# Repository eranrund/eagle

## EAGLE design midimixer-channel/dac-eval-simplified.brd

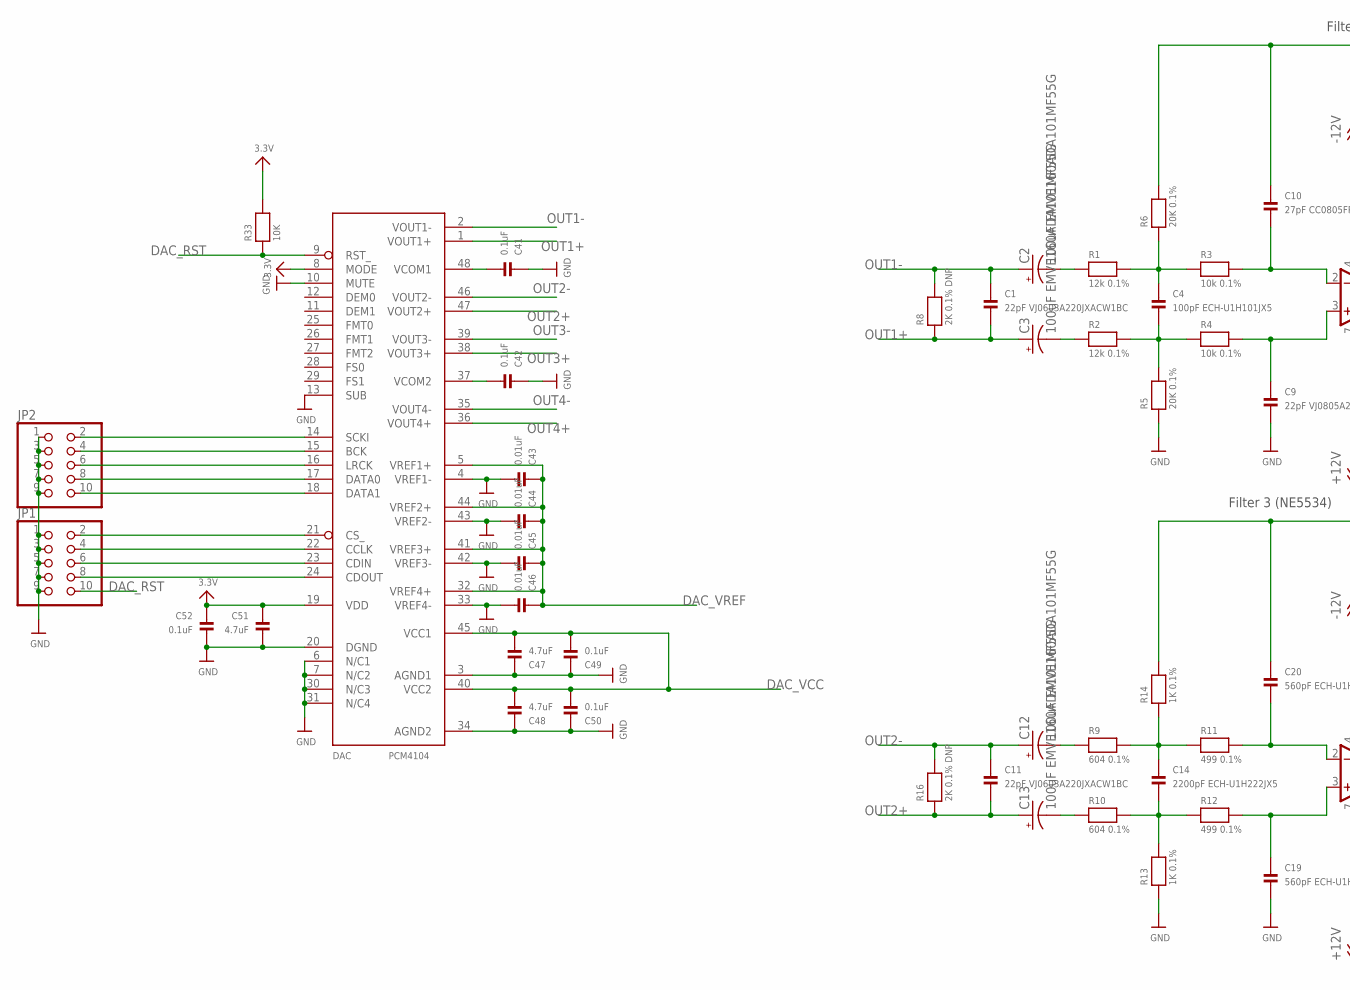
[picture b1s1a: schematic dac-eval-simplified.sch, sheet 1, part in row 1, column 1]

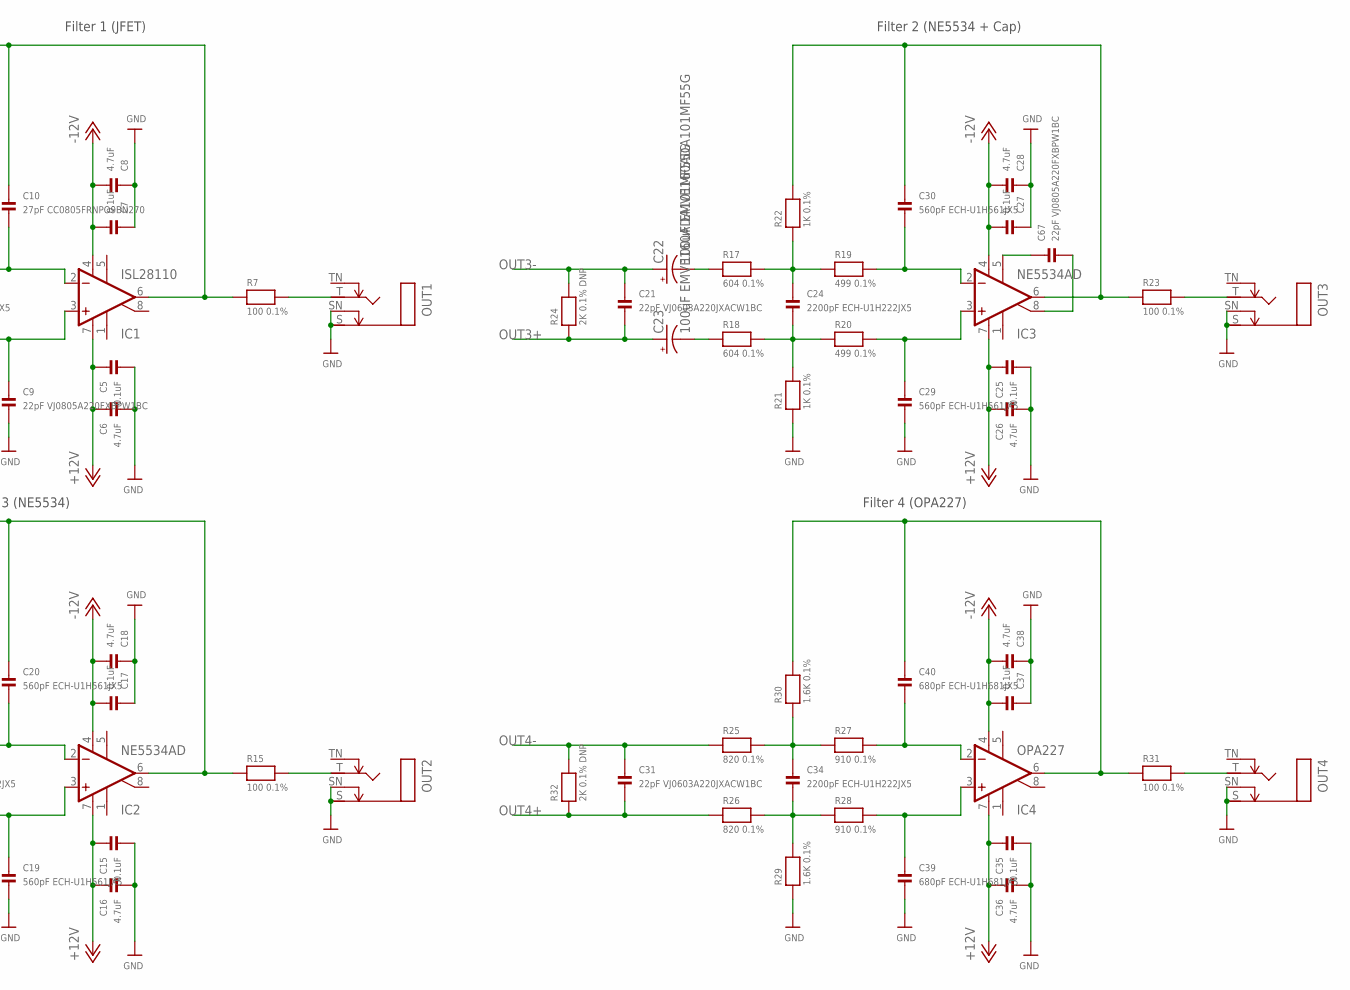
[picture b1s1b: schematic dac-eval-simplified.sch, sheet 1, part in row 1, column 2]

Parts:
C1, C11, C21, C31: 22pF VJ0603A220JXACW1BC; 0603
C2, C3, C12, C13, C22, C23: 100uF EMVE160ADA101MF55G; PANASONIC_D
C4: 100pF ECH-U1H101JX5; 0805
C5, C7, C15, C17, C25, C27, C35, C37, C41, C42, C49, C50, C52: 0.1uF; 0603
C6, C8, C16, C18, C26, C28, C36, C38, C47, C48, C51: 4.7uF; 0603
C9, C67: 22pF VJ0805A220FXBPW1BC; 0805
C10: 27pF CC0805FRNPO9BN270; 0805
C14, C24, C34: 2200pF ECH-U1H222JX5; 0805
C19, C20, C29, C30: 560pF ECH-U1H561JX5; 0805
C39, C40: 680pF ECH-U1H681JX5; 0805
C43, C44, C45, C46: 0.01uF; 0603
DAC: PCM4104; SQFP-S-7X7-48
IC1: ISL28110; SO08
IC2, IC3: NE5534AD; SO08
IC4: OPA227; SO08
JP1, JP2: HEADER-2X5; 2X05
OUT1, OUT2, OUT3, OUT4: NMJ4HFD2; NMJ4HC-S
R1, R2: 12k 0.1%; 0603
R3, R4: 10k 0.1%; 0603
R5, R6: 20K 0.1%; 0603
R7, R15, R23, R31: 100 0.1%; 0603
R8, R16, R24, R32: 2K 0.1% DNP; 0603
R9, R10, R17, R18: 604 0.1%; 0603
R11, R12, R19, R20: 499 0.1%; 0603
R13, R14, R21, R22: 1K 0.1%; 0603
R25, R26: 820 0.1%; 0603
R27, R28: 910 0.1%; 0603
R29, R30: 1.6K 0.1%; 0603
R33: 10K; 0603

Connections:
3.3V: C51.1, C52.1, DAC.8 (MODE), DAC.19 (VDD), R33.2; also elsewhere on the board
+12V: C5.1, C6.1, C15.1, C16.1, C25.1, C26.1, C35.1, C36.1, IC1.7 (V+), IC2.7 (V+), IC3.7 (V+), IC4.7 (V+); also elsewhere on the board
-12V: C7.2, C8.2, C17.2, C18.2, C27.2, C28.2, C37.2, C38.2, IC1.4 (V-), IC2.4 (V-), IC3.4 (V-), IC4.4 (V-); also elsewhere on the board
DAC_BCK: DAC.15 (BCK), JP2.4
DAC_CLK: DAC.22 (CCLK), JP1.4
DAC_CS: DAC.21 (CS_), JP1.2
DAC_D0: DAC.17 (DATA0), JP2.8
DAC_D1: DAC.18 (DATA1), JP2.10
DAC_LRCK: DAC.16 (LRCK), JP2.6
DAC_MISO: DAC.24 (CDOUT), JP1.8
DAC_MOSI: DAC.23 (CDIN), JP1.6
DAC_RST: DAC.9 (RST_), JP1.10, R33.1
DAC_SCK: DAC.14 (SCKI), JP2.2
DAC_VCC: C47.2, C48.2, C49.2, C50.2, DAC.40 (VCC2), DAC.45 (VCC1); also elsewhere on the board
DAC_VREF: C43.1, C44.1, C45.1, C46.1, DAC.5 (VREF1+), DAC.32 (VREF4+), DAC.41 (VREF3+), DAC.44 (VREF2+); also elsewhere on the board
GND: C5.2, C6.2, C7.1, C8.1, C9.2, C15.2, C16.2, C17.1, C18.1, C19.2, C25.2, C26.2, C27.1, C28.1, C29.2, C35.2, C36.2, C37.1, C38.1, C39.2, C41.1, C42.1, C43.2, C44.2, C45.2, C46.2, C47.1, C48.1, C49.1, C50.1, C51.2, C52.2, DAC.3 (AGND1), DAC.4 (VREF1-), DAC.6 (N/C1), DAC.7 (N/C2), DAC.10 (MUTE), DAC.13 (SUB), DAC.20 (DGND), DAC.30 (N/C3), DAC.31 (N/C4), DAC.33 (VREF4-), DAC.34 (AGND2), DAC.42 (VREF3-), DAC.43 (VREF2-), JP1.1, JP1.3, JP1.5, JP1.7, JP1.9, JP2.1, JP2.3, JP2.5, JP2.7, JP2.9, OUT1.S, OUT1.SN, OUT2.S, OUT2.SN, OUT3.S, OUT3.SN, OUT4.S, OUT4.SN, R5.1, R13.1, R21.1, R29.1; also elsewhere on the board
unnamed: C12.-, R9.1
unnamed: C13.-, R10.1
unnamed: C2.-, R1.1
unnamed: C3.-, R2.1
unnamed: C4.2, R2.2, R4.1, R5.2
unnamed: C4.1, R1.2, R3.1, R6.1
unnamed: C14.2, R10.2, R12.1, R13.2
unnamed: C9.1, IC1.3 (+IN), R4.2
unnamed: C10.2, IC1.2 (-IN), R3.2
unnamed: C10.1, IC1.6 (OUT), R6.2, R7.1
unnamed: C14.1, R9.2, R11.1, R14.1
unnamed: OUT1.T, R7.2
unnamed: C19.1, IC2.3 (+IN), R12.2
unnamed: C20.2, IC2.2 (-IN), R11.2
unnamed: C20.1, IC2.6 (OUT), R14.2, R15.1
unnamed: OUT2.T, R15.2
unnamed: C22.-, R17.1
unnamed: C23.-, R18.1
unnamed: C24.2, R18.2, R20.1, R21.2
unnamed: C24.1, R17.2, R19.1, R22.1
unnamed: C29.1, IC3.3 (+IN), R20.2
unnamed: C30.2, IC3.2 (-IN), R19.2
unnamed: C30.1, IC3.6 (OUT), R22.2, R23.1
unnamed: OUT3.T, R23.2
unnamed: C34.2, R26.2, R28.1, R29.2
unnamed: C34.1, R25.2, R27.1, R30.1
unnamed: C39.1, IC4.3 (+IN), R28.2
unnamed: C40.2, IC4.2 (-IN), R27.2
unnamed: C40.1, IC4.6 (OUT), R30.2, R31.1
unnamed: OUT4.T, R31.2
unnamed: C41.2, DAC.48 (VCOM1)
unnamed: C42.2, DAC.37 (VCOM2)
unnamed: C67.1, IC3.5 (CMP)
unnamed: C67.2, IC3.8 (ON/CMP)
OUT1+: C1.2, C3.+, DAC.1 (VOUT1+), R8.1
OUT1-: C1.1, C2.+, DAC.2 (VOUT1-), R8.2
OUT2+: C11.2, C13.+, DAC.47 (VOUT2+), R16.1
OUT2-: C11.1, C12.+, DAC.46 (VOUT2-), R16.2
OUT3+: C21.2, C23.+, DAC.38 (VOUT3+), R24.1
OUT3-: C21.1, C22.+, DAC.39 (VOUT3-), R24.2
OUT4+: C31.2, DAC.36 (VOUT4+), R26.1, R32.1
OUT4-: C31.1, DAC.35 (VOUT4-), R25.1, R32.2

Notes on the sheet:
Filter 1 (JFET)
Filter 2 (NE5534 + Cap)
Filter 3 (NE5534)
Filter 4 (OPA227)

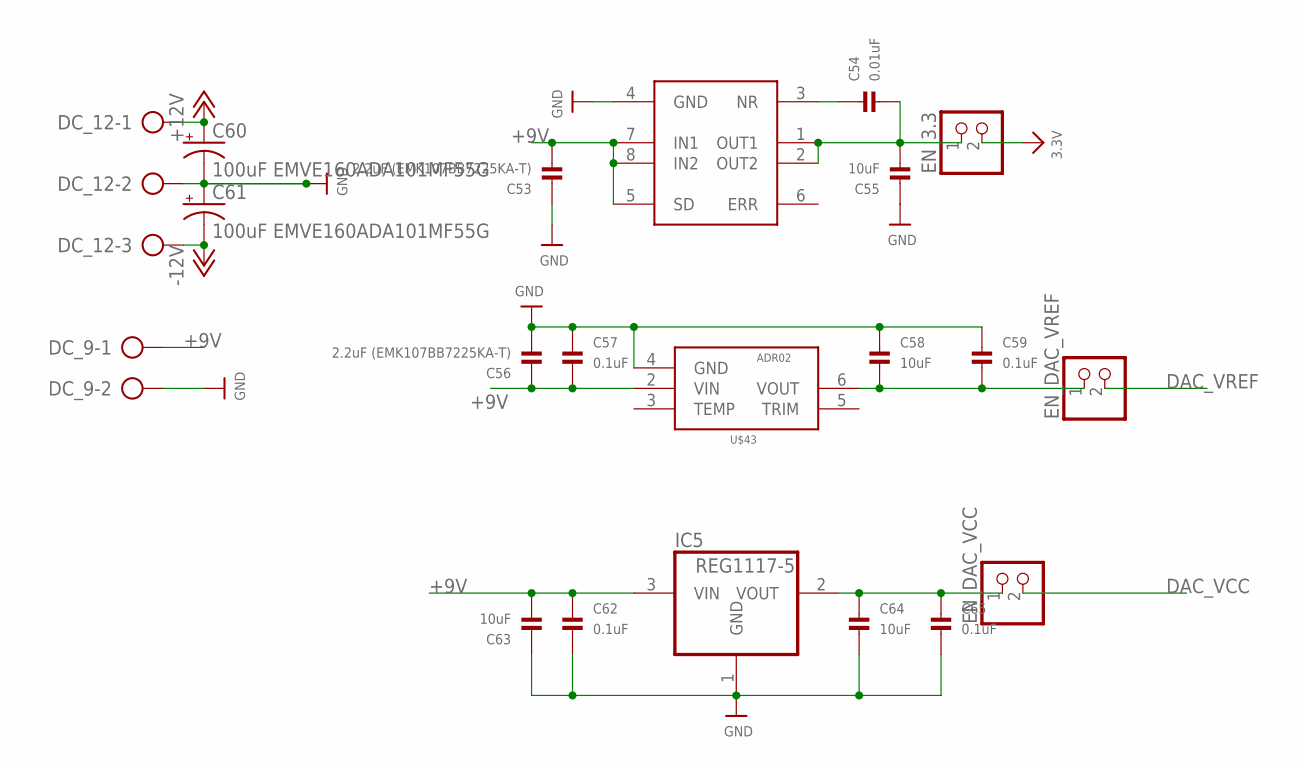
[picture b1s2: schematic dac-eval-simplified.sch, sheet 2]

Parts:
C53, C56: 2.2uF (EMK107BB7225KA-T); 0603
C54: 0.01uF; 0603
C55, C58, C63, C64: 10uF; 0603
C57, C59, C62, C65: 0.1uF; 0603
C60, C61: 100uF EMVE160ADA101MF55G; PANASONIC_D
DC_9: AK500/2
DC_12: AK500/3
EN_3.3: HEADER-1X2; 1X02_OVAL
EN_DAC_VCC: HEADER-1X2; 1X02_OVAL
EN_DAC_VREF: HEADER-1X2; 1X02_OVAL
IC5: REG1117-5; SOT223
U$30: ADP3301ARZ-3.3; SO08
U$43: ADR02; SOIC8

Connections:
3.3V: EN_3.3.2; also elsewhere on the board
+9V: C53.2, C56.1, C57.2, C62.1, C63.2, DC_9.1, IC5.3 (VIN), U$30.5 (SD), U$30.7 (IN1), U$30.8 (IN2), U$43.2 (VIN)
+12V: C60.+, DC_12.1; also elsewhere on the board
-12V: C61.-, DC_12.3; also elsewhere on the board
DAC_VCC: EN_DAC_VCC.2; also elsewhere on the board
DAC_VREF: EN_DAC_VREF.2; also elsewhere on the board
GND: C53.1, C55.1, C56.2, C57.1, C58.1, C59.1, C60.-, C61.+, C62.2, C63.1, C64.2, C65.2, DC_9.2, DC_12.2, IC5.1 (GND), U$30.4 (GND), U$43.4 (GND); also elsewhere on the board
unnamed: C54.2, C55.2, EN_3.3.1, U$30.1 (OUT1), U$30.2 (OUT2)
unnamed: C54.1, U$30.3 (NR)
unnamed: C58.2, C59.2, EN_DAC_VREF.1, U$43.6 (VOUT)
unnamed: C64.1, C65.1, EN_DAC_VCC.1, IC5.2 (VOUT)

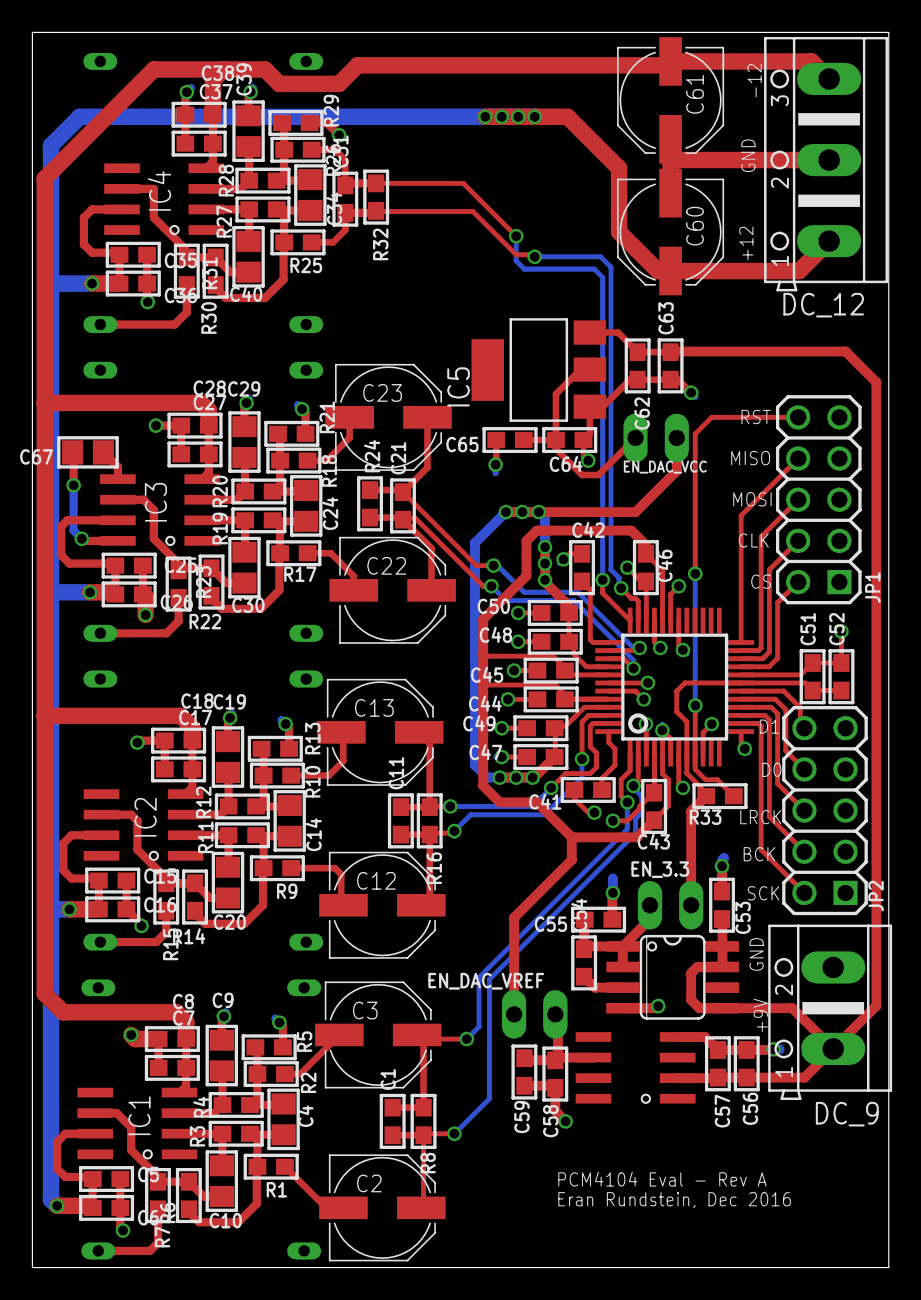
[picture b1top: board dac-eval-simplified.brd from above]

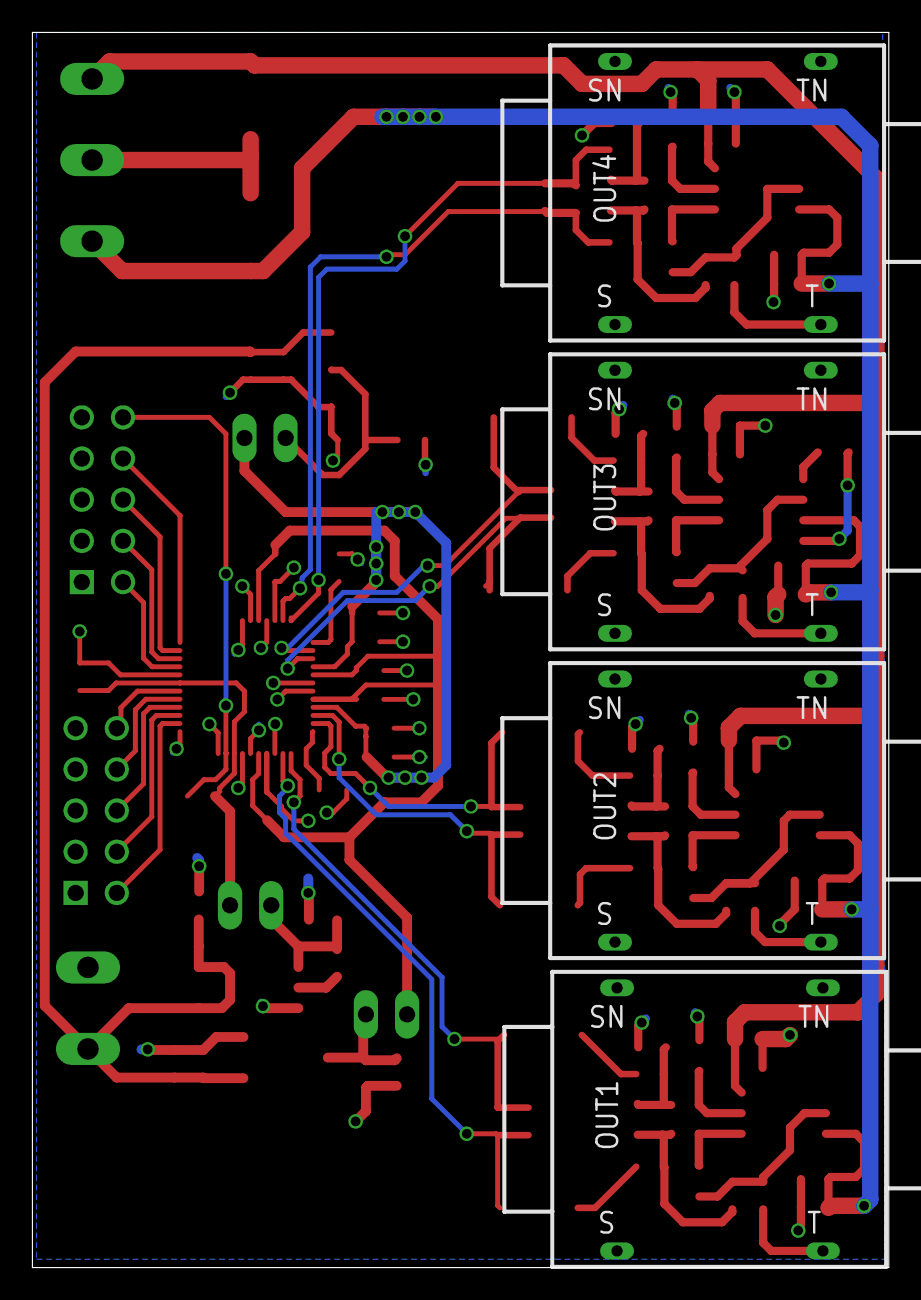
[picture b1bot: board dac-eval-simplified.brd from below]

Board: 2 copper layers, 52.8 x 76.2 mm, 116 parts (4 on the bottom side), 63 nets.

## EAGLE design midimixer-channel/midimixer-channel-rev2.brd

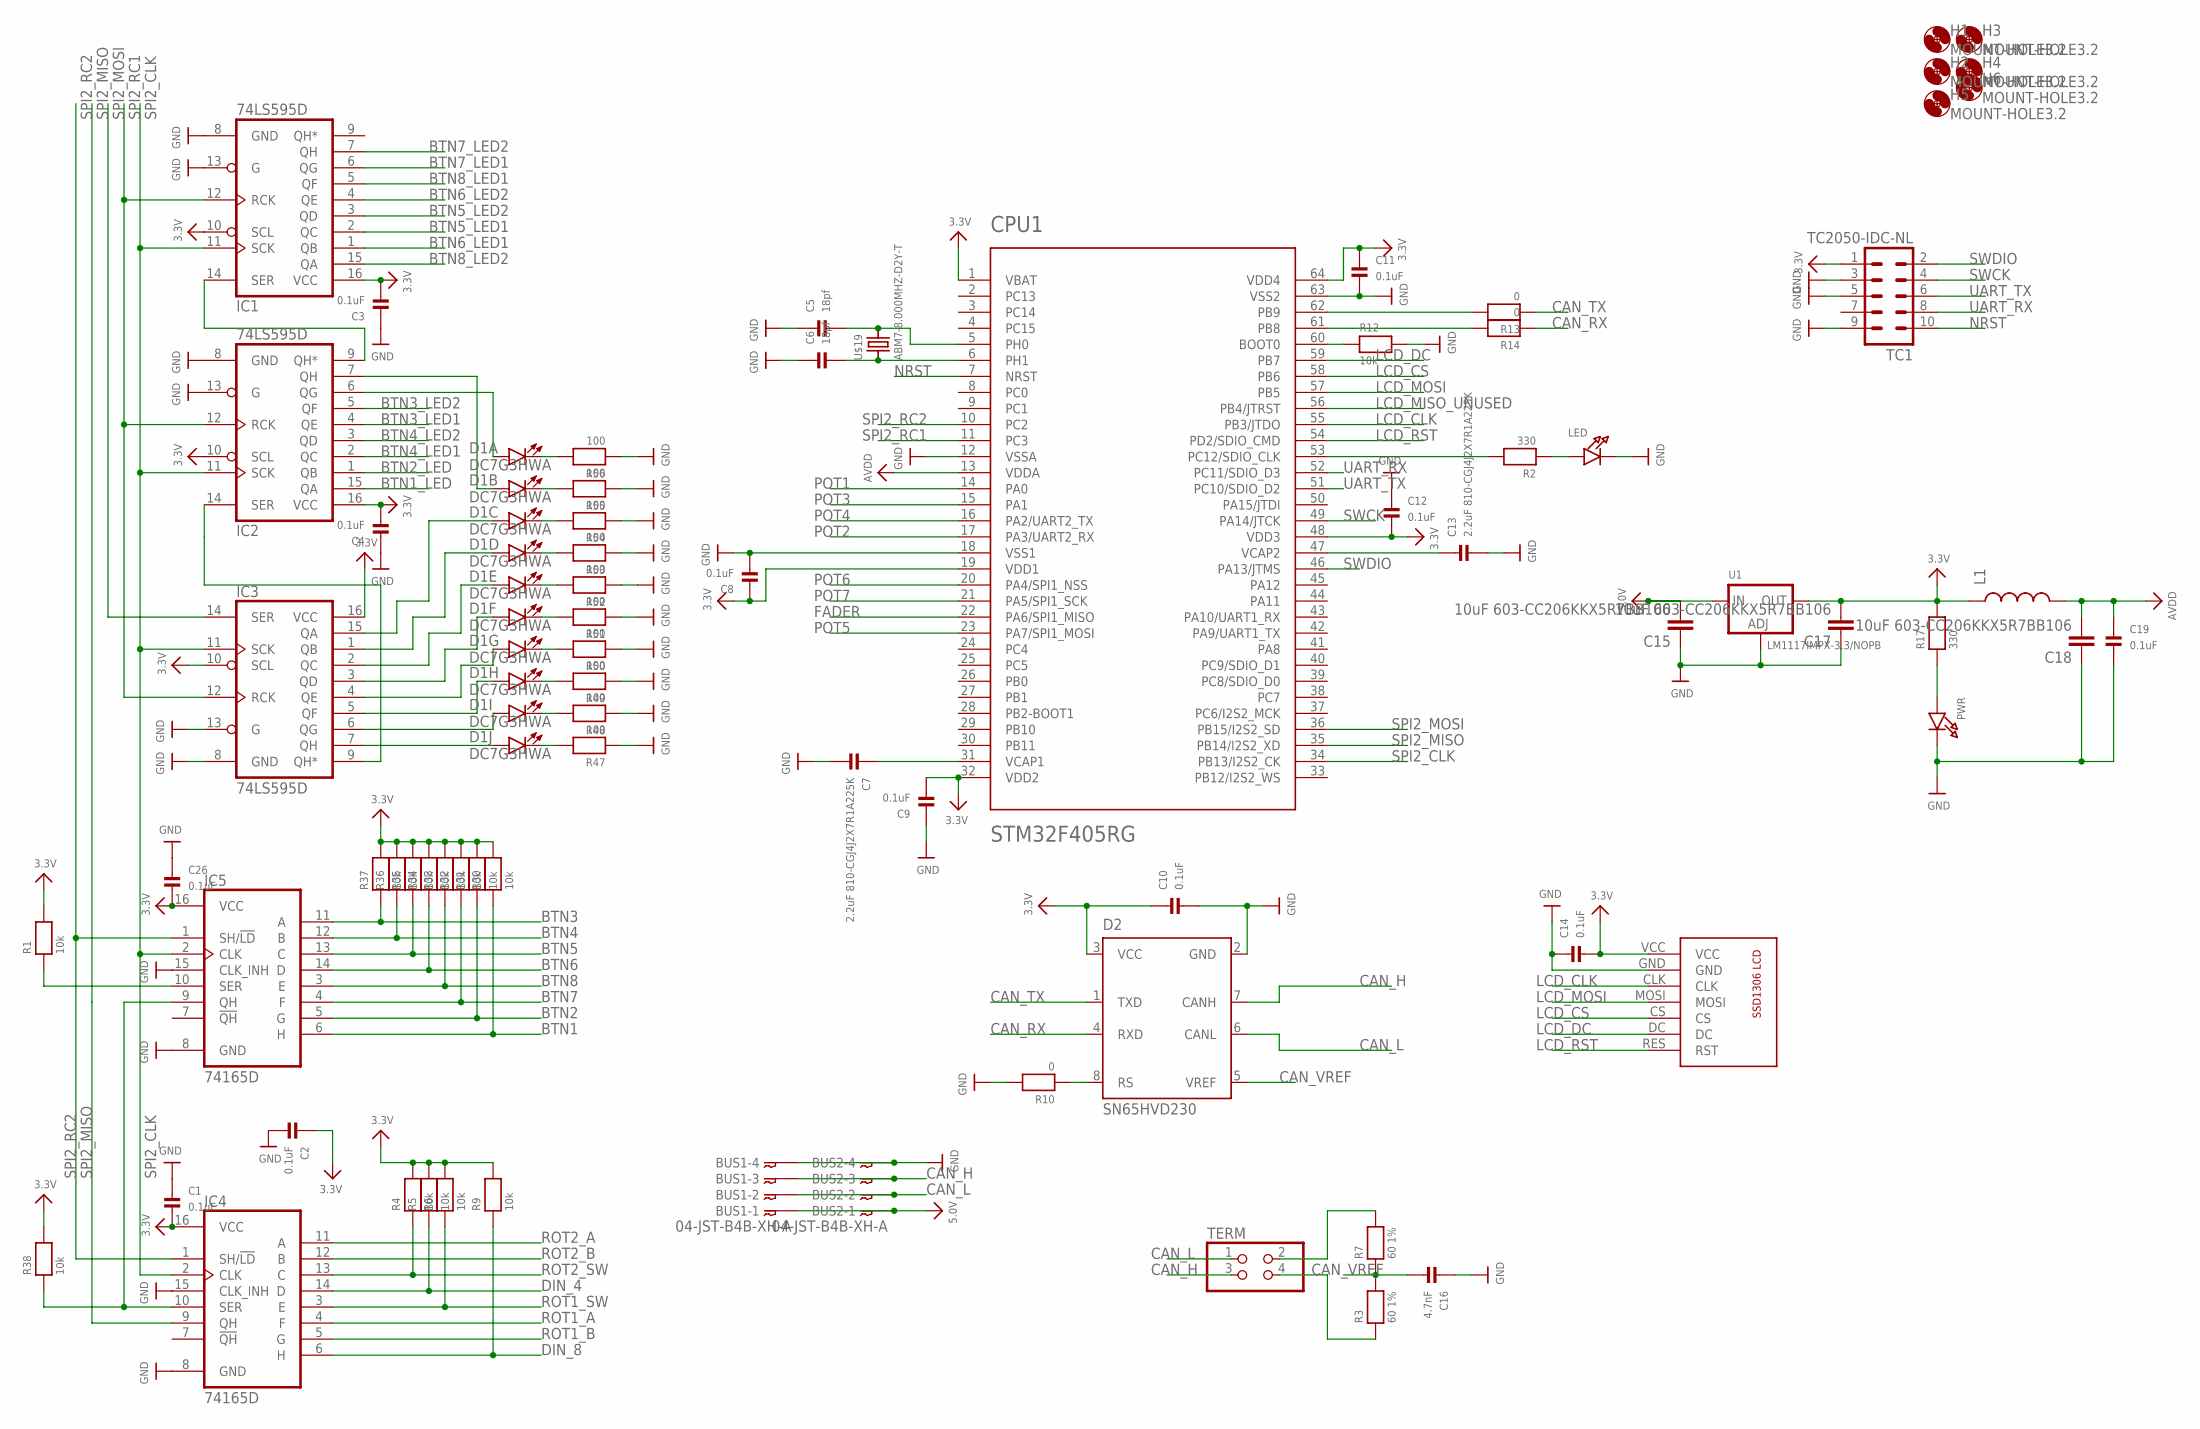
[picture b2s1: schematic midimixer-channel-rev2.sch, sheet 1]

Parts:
BUS1, BUS2: 04-JST-B4B-XH-A; B4B-XH
C1, C2, C3, C4, C8, C9, C10, C11, C12, C14, C19, C26: 0.1uF; 0603
C5, C6: 18pf; 0603
C7, C13: 2.2uF 810-CGJ4J2X7R1A225K; 0805; MPN CGJ4J2X7R1A225K125AA
C15, C17, C18: 10uF 603-CC206KKX5R7BB106; 1206; MPN CC1206KKX5R7BB106
C16: 4.7nF; 0603
CPU1: STM32F405RG; TQFP64; MPN STM32F405RGT6
D1: DC7G3HWA; LED_BARGAPH_10
D2: SN65HVD230; SO8
H1, H2, H3, H4, H5, H6: MOUNT-HOLE3.2; 3,2
IC1, IC2, IC3: 74LS595D; SO16
IC4, IC5: 74165D; SO16
L1: INDUCTOR0805; 0805; MPN 2508056017Y2
LCD: SSD1306-7PINWITHOUT-HOLES; SSD1306-7PIN-NO-HOLES
LED: LED0603; CHIPLED_0603
PWR: LED0603; CHIPLED_0603
R1, R4, R5, R6, R9, R12, R30, R31, R32, R33, R34, R35, R36, R37, R38: 10k; _0603
R2, R17: 330; 0603
R3, R7: 60 1%; 0603; MPN MF-RES-0603-60.4
R10, R13, R14: 0; _0603
R47, R48, R49, R50, R51, R52, R53, R54, R55, R56: 100; _0603
TC1: TC2050-IDC-NL
TERM: PINHD-2X2; 2X02
U1: LM1117IMPX-3.3/NOPB; SOT223-R
U$19: ABM7-8.000MHZ-D2Y-T

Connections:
3.3V: C1.2, C2.1, C3.2, C4.2, C8.1, C9.2, C10.1, C11.1, C12.2, C14.2, C17.2, C26.2, CPU1.1 (VBAT), CPU1.19 (VDD1), CPU1.32 (VDD2), CPU1.48 (VDD3), CPU1.64 (VDD4), D2.3 (VCC), IC1.10 (SCL), IC1.16 (VCC), IC2.10 (SCL), IC2.16 (VCC), IC3.10 (SCL), IC3.16 (VCC), IC4.16 (VCC), IC5.16 (VCC), L1.1, LCD.VCC, R1.2, R4.2, R5.2, R6.2, R9.2, R17.2, R30.2, R31.2, R32.2, R33.2, R34.2, R35.2, R36.2, R37.2, R38.2, TC1.1, U1.2 (OUT); also elsewhere on the board
5.0V: BUS1.P$1, BUS2.P$1, C15.2, U1.3 (IN); also elsewhere on the board
AVDD: C18.2, C19.1, CPU1.13 (VDDA), L1.2
BTN1: IC5.6 (H), R30.1; also elsewhere on the board
BTN1_LED: IC2.15 (QA); also elsewhere on the board
BTN2: IC5.5 (G), R31.1; also elsewhere on the board
BTN2_LED: IC2.1 (QB); also elsewhere on the board
BTN3: IC5.11 (A), R37.1; also elsewhere on the board
BTN3_LED1: IC2.4 (QE); also elsewhere on the board
BTN3_LED2: IC2.5 (QF); also elsewhere on the board
BTN4: IC5.12 (B), R36.1; also elsewhere on the board
BTN4_LED1: IC2.2 (QC); also elsewhere on the board
BTN4_LED2: IC2.3 (QD); also elsewhere on the board
BTN5: IC5.13 (C), R35.1; also elsewhere on the board
BTN5_LED1: IC1.2 (QC); also elsewhere on the board
BTN5_LED2: IC1.3 (QD); also elsewhere on the board
BTN6: IC5.14 (D), R34.1; also elsewhere on the board
BTN6_LED1: IC1.1 (QB); also elsewhere on the board
BTN6_LED2: IC1.4 (QE); also elsewhere on the board
BTN7: IC5.4 (F), R32.1; also elsewhere on the board
BTN7_LED1: IC1.6 (QG); also elsewhere on the board
BTN7_LED2: IC1.7 (QH); also elsewhere on the board
BTN8: IC5.3 (E), R33.1; also elsewhere on the board
BTN8_LED1: IC1.5 (QF); also elsewhere on the board
BTN8_LED2: IC1.15 (QA); also elsewhere on the board
CAN_H: BUS1.P$3, BUS2.P$3, D2.7 (CANH), TERM.3
CAN_L: BUS1.P$2, BUS2.P$2, D2.6 (CANL), TERM.1
CAN_RX: D2.4 (RXD), R14.1
CAN_TX: D2.1 (TXD), R13.1
CAN_VREF: C16.2, D2.5 (VREF), R3.2, R7.1
DIN_4: IC4.14 (D), R5.1
DIN_8: IC4.6 (H), R9.1
FADER: CPU1.22 (PA6/SPI1_MISO); also elsewhere on the board
GND: BUS1.P$4, BUS2.P$4, C1.1, C2.2, C3.1, C4.1, C5.1, C6.1, C7.2, C8.2, C9.1, C10.2, C11.2, C12.1, C13.2, C14.1, C15.1, C16.1, C17.1, C18.1, C19.2, C26.1, CPU1.12 (VSSA), CPU1.18 (VSS1), CPU1.63 (VSS2), D2.2 (GND), IC1.8 (GND), IC1.13 (G), IC2.8 (GND), IC2.13 (G), IC3.8 (GND), IC3.13 (G), IC4.8 (GND), IC4.15 (CLK_INH), IC5.8 (GND), IC5.15 (CLK_INH), LCD.GND, LED.C, PWR.C, R10.2, R12.2, R47.1, R48.1, R49.1, R50.1, R51.1, R52.1, R53.1, R54.1, R55.1, R56.1, TC1.3, TC1.5, TC1.9, U1.1 (ADJ); also elsewhere on the board
LCD_CLK: CPU1.55 (PB3/JTDO), LCD.CLK
LCD_CS: CPU1.58 (PB6), LCD.CS
LCD_DC: CPU1.59 (PB7), LCD.DC
LCD_MISO_UNUSED: CPU1.56 (PB4/JTRST)
LCD_MOSI: CPU1.57 (PB5), LCD.MOSI
LCD_RST: CPU1.54 (PD2/SDIO_CMD), LCD.RES (RST)
unnamed: C6.2, CPU1.6 (PH1), U$19.P$1 (1)
unnamed: C5.2, CPU1.5 (PH0), U$19.P$2 (2)
unnamed: C13.1, CPU1.47 (VCAP2)
unnamed: C7.1, CPU1.31 (VCAP1)
unnamed: PWR.A, R17.1
unnamed: CPU1.60 (BOOT0), R12.1
unnamed: D1.5 (A), IC3.2 (QC)
unnamed: D1.2 (A), IC2.7 (QH)
unnamed: D1.1 (A), IC2.6 (QG)
unnamed: IC1.14 (SER), IC2.9 (QH*)
unnamed: CPU1.62 (PB9), R13.2
unnamed: D1.11 (C), R47.2
unnamed: D1.12 (C), R48.2
unnamed: D1.13 (C), R49.2
unnamed: D1.14 (C), R50.2
unnamed: D1.15 (C), R51.2
unnamed: D1.16 (C), R52.2
unnamed: D1.17 (C), R53.2
unnamed: D1.18 (C), R54.2
unnamed: D1.19 (C), R55.2
unnamed: D1.20 (C), R56.2
unnamed: IC4.10 (SER), IC5.9 (QH), R38.1
unnamed: CPU1.61 (PB8), R14.2
unnamed: IC5.10 (SER), R1.1
unnamed: LED.A, R2.1
unnamed: D1.10 (A), IC3.7 (QH)
unnamed: D1.9 (A), IC3.6 (QG)
unnamed: D1.8 (A), IC3.5 (QF)
unnamed: CPU1.53 (PC12/SDIO_CLK), R2.2
unnamed: R7.2, TERM.2
unnamed: R3.1, TERM.4
unnamed: D1.7 (A), IC3.4 (QE)
unnamed: D1.6 (A), IC3.3 (QD)
unnamed: D1.4 (A), IC3.1 (QB)
unnamed: D1.3 (A), IC3.15 (QA)
unnamed: IC2.14 (SER), IC3.9 (QH*)
unnamed: D2.8 (RS), R10.1
NRST: CPU1.7 (NRST), TC1.10
POT1: CPU1.14 (PA0); also elsewhere on the board
POT2: CPU1.17 (PA3/UART2_RX); also elsewhere on the board
POT3: CPU1.15 (PA1); also elsewhere on the board
POT4: CPU1.16 (PA2/UART2_TX); also elsewhere on the board
POT5: CPU1.23 (PA7/SPI1_MOSI); also elsewhere on the board
POT6: CPU1.20 (PA4/SPI1_NSS); also elsewhere on the board
POT7: CPU1.21 (PA5/SPI1_SCK); also elsewhere on the board
ROT1_A: IC4.4 (F); also elsewhere on the board
ROT1_B: IC4.5 (G); also elsewhere on the board
ROT1_SW: IC4.3 (E), R6.1; also elsewhere on the board
ROT2_A: IC4.11 (A); also elsewhere on the board
ROT2_B: IC4.12 (B); also elsewhere on the board
ROT2_SW: IC4.13 (C), R4.1; also elsewhere on the board
SPI2_CLK: CPU1.34 (PB13/I2S2_CK), IC1.11 (SCK), IC2.11 (SCK), IC3.11 (SCK), IC4.2 (CLK), IC5.2 (CLK)
SPI2_MISO: CPU1.35 (PB14/I2S2_XD), IC4.9 (QH)
SPI2_MOSI: CPU1.36 (PB15/I2S2_SD), IC3.14 (SER)
SPI2_RC1: CPU1.11 (PC3), IC1.12 (RCK), IC2.12 (RCK), IC3.12 (RCK)
SPI2_RC2: CPU1.10 (PC2), IC4.1 (SH/!LD), IC5.1 (SH/!LD)
SWCK: CPU1.49 (PA14/JTCK), TC1.4
SWDIO: CPU1.46 (PA13/JTMS), TC1.2
UART_RX: CPU1.52 (PC11/SDIO_D3), TC1.8
UART_TX: CPU1.51 (PC10/SDIO_D2), TC1.6

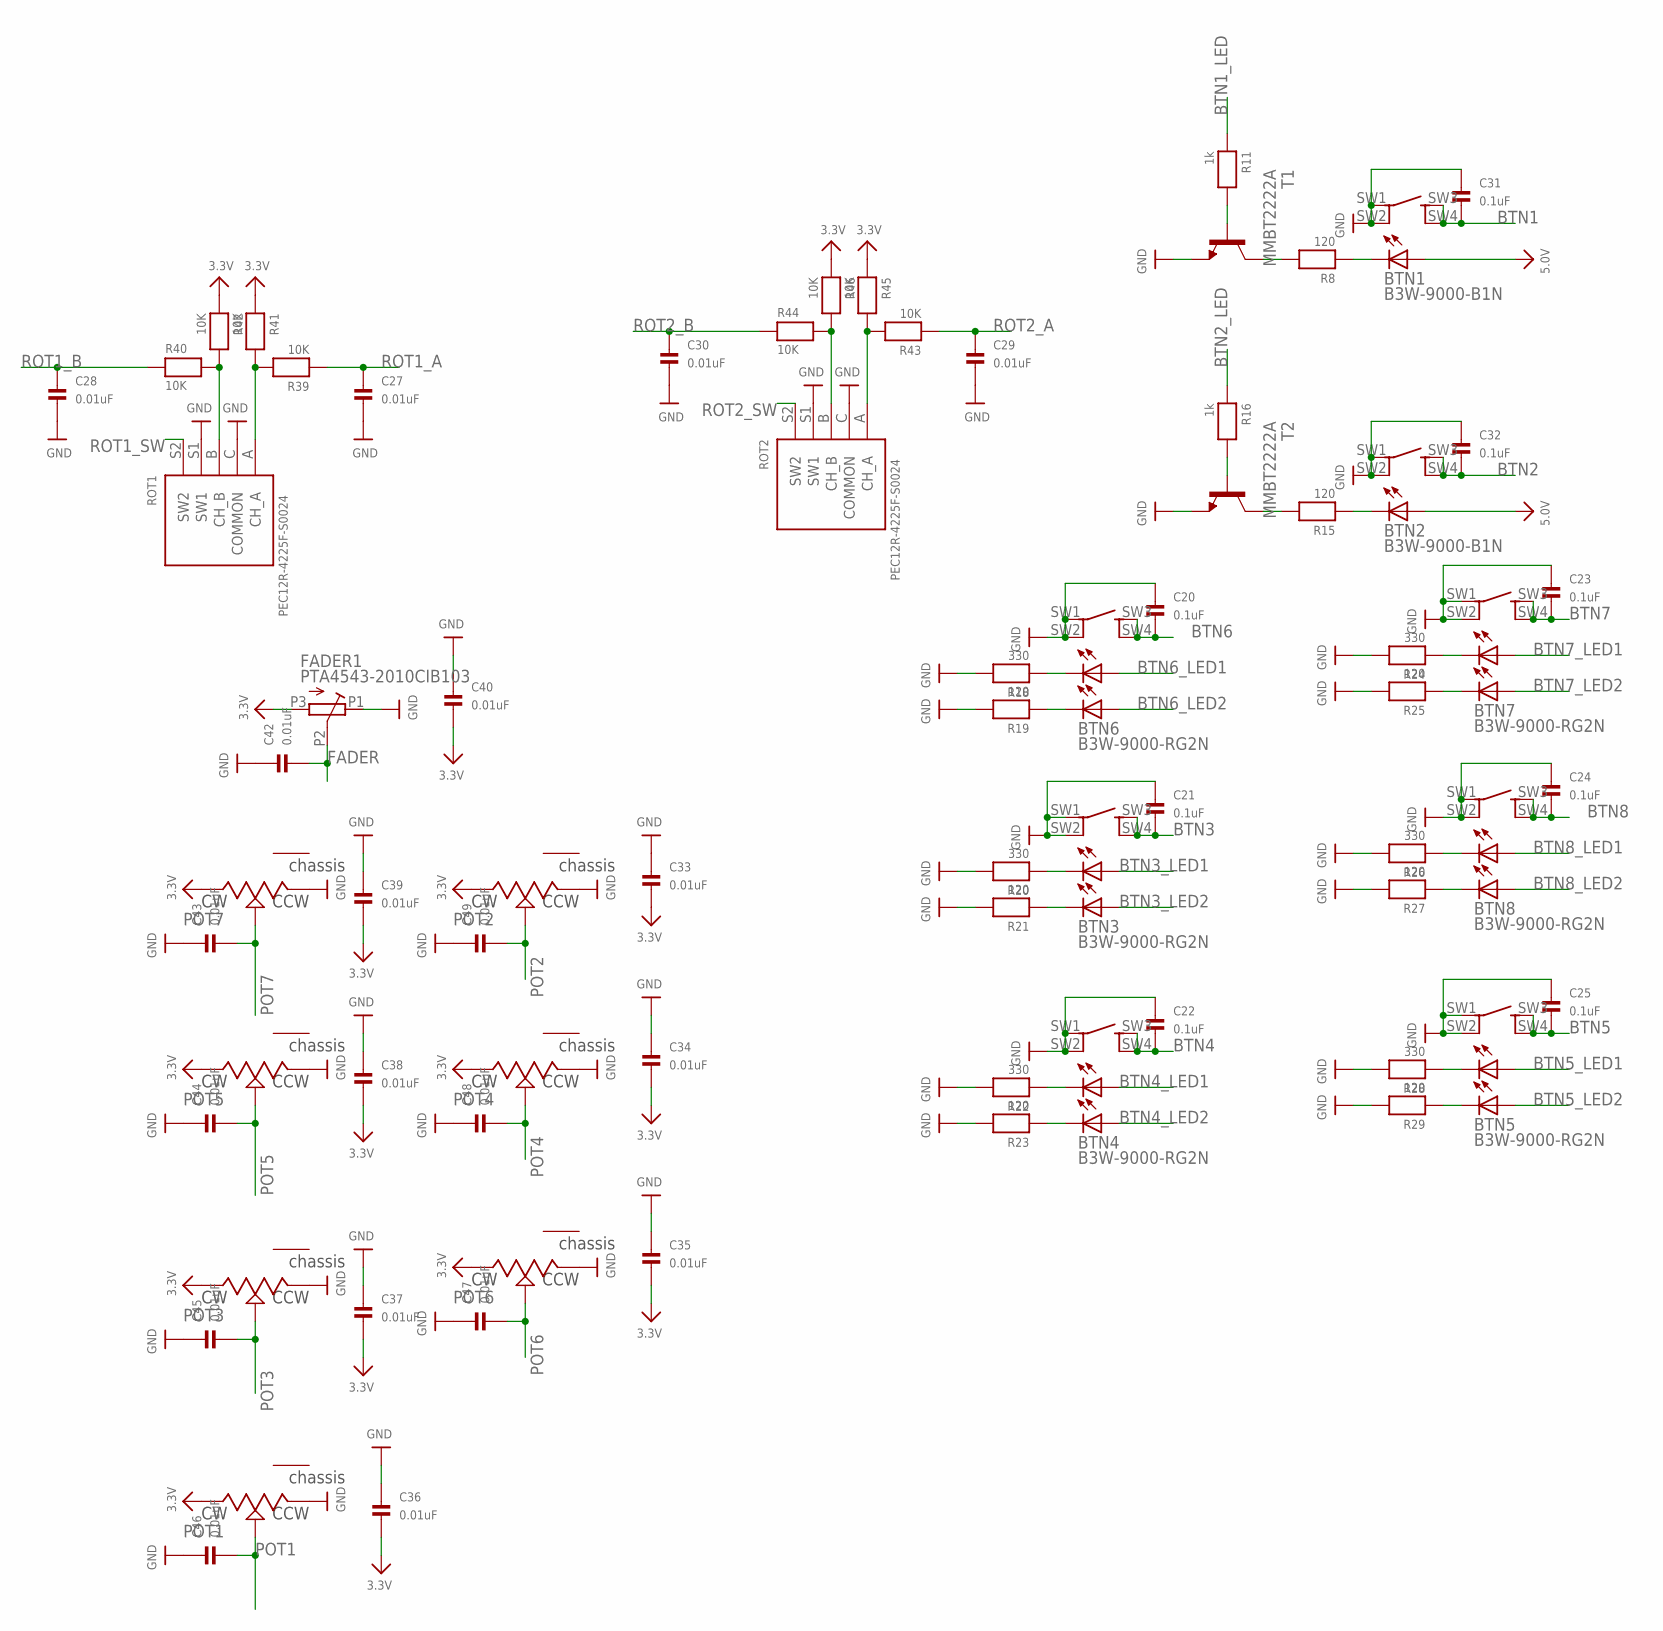
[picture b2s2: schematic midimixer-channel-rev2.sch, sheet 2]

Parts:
BTN1, BTN2: B3W-9000-B1N; B3W-9000-X1X
BTN3, BTN4, BTN5, BTN6, BTN7, BTN8: B3W-9000-RG2N; B3W-9000-X2X
C20, C21, C22, C23, C24, C25, C31, C32: 0.1uF; 0603
C27, C28, C29, C30, C33, C34, C35, C36, C37, C38, C39, C40, C42, C43, C44, C45, C46, C47, C48, C49: 0.01uF; 0603
FADER1: PTA4543-2010CIB103; PTA4543-2015CPB103
POT1, POT2, POT3, POT4, POT5, POT6, POT7: POTENTIOMETERPTV09A_VERTICAL; PTV09A-4
R8, R15, R19, R21, R23, R25, R27, R29: 120; 0603
R11, R16: 1k; 0603
R18, R20, R22, R24, R26, R28: 330; 0603
R39, R40, R41, R42, R43, R44, R45, R46: 10K; 0603
ROT1, ROT2: PEC12R-4225F-S0024; PEC111-4XXXK-SXXXX
T1, T2: MMBT2222A; SOT23-BEC

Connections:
3.3V: C33.2, C34.2, C35.2, C36.2, C37.2, C38.2, C39.2, C40.2, FADER1.P3 (E), POT1.CW, POT2.CW, POT3.CW, POT4.CW, POT5.CW, POT6.CW, POT7.CW, R41.1, R42.1, R45.1, R46.1; also elsewhere on the board
5.0V: BTN1.LED1+, BTN2.LED1+; also elsewhere on the board
BTN1: BTN1.SW3 (SW2_A), BTN1.SW4 (SW2_B), C31.2; also elsewhere on the board
BTN1_LED: R11.1; also elsewhere on the board
BTN2: BTN2.SW3 (SW2_A), BTN2.SW4 (SW2_B), C32.2; also elsewhere on the board
BTN2_LED: R16.1; also elsewhere on the board
BTN3: BTN3.SW3 (SW2_A), BTN3.SW4 (SW2_B), C21.2; also elsewhere on the board
BTN3_LED1: BTN3.LED1+; also elsewhere on the board
BTN3_LED2: BTN3.LED2+; also elsewhere on the board
BTN4: BTN4.SW3 (SW2_A), BTN4.SW4 (SW2_B), C22.2; also elsewhere on the board
BTN4_LED1: BTN4.LED1+; also elsewhere on the board
BTN4_LED2: BTN4.LED2+; also elsewhere on the board
BTN5: BTN5.SW3 (SW2_A), BTN5.SW4 (SW2_B), C25.2; also elsewhere on the board
BTN5_LED1: BTN5.LED1+; also elsewhere on the board
BTN5_LED2: BTN5.LED2+; also elsewhere on the board
BTN6: BTN6.SW3 (SW2_A), BTN6.SW4 (SW2_B), C20.2; also elsewhere on the board
BTN6_LED1: BTN6.LED1+; also elsewhere on the board
BTN6_LED2: BTN6.LED2+; also elsewhere on the board
BTN7: BTN7.SW3 (SW2_A), BTN7.SW4 (SW2_B), C23.2; also elsewhere on the board
BTN7_LED1: BTN7.LED1+; also elsewhere on the board
BTN7_LED2: BTN7.LED2+; also elsewhere on the board
BTN8: BTN8.SW3 (SW2_A), BTN8.SW4 (SW2_B), C24.2; also elsewhere on the board
BTN8_LED1: BTN8.LED1+; also elsewhere on the board
BTN8_LED2: BTN8.LED2+; also elsewhere on the board
FADER: C42.2, FADER1.P2 (S); also elsewhere on the board
GND: BTN1.SW1 (SW1_A), BTN1.SW2 (SW1_B), BTN2.SW1 (SW1_A), BTN2.SW2 (SW1_B), BTN3.SW1 (SW1_A), BTN3.SW2 (SW1_B), BTN4.SW1 (SW1_A), BTN4.SW2 (SW1_B), BTN5.SW1 (SW1_A), BTN5.SW2 (SW1_B), BTN6.SW1 (SW1_A), BTN6.SW2 (SW1_B), BTN7.SW1 (SW1_A), BTN7.SW2 (SW1_B), BTN8.SW1 (SW1_A), BTN8.SW2 (SW1_B), C20.1, C21.1, C22.1, C23.1, C24.1, C25.1, C27.2, C28.2, C29.2, C30.2, C31.1, C32.1, C33.1, C34.1, C35.1, C36.1, C37.1, C38.1, C39.1, C40.1, C42.1, C43.1, C44.1, C45.1, C46.1, C47.1, C48.1, C49.1, FADER1.P1 (A), POT1.CCW, POT2.CCW, POT3.CCW, POT4.CCW, POT5.CCW, POT6.CCW, POT7.CCW, R18.2, R19.2, R20.2, R21.2, R22.2, R23.2, R24.2, R25.2, R26.2, R27.2, R28.2, R29.2, ROT1.C (COMMON), ROT1.S1 (SW1), ROT2.C (COMMON), ROT2.S1 (SW1), T1.E, T2.E; also elsewhere on the board
unnamed: BTN6.LED1-, R18.1
unnamed: BTN6.LED2-, R19.1
unnamed: BTN3.LED1-, R20.1
unnamed: BTN3.LED2-, R21.1
unnamed: BTN7.LED1-, R24.1
unnamed: BTN7.LED2-, R25.1
unnamed: R40.2, R42.2, ROT1.B (CH_B)
unnamed: R39.2, R41.2, ROT1.A (CH_A)
unnamed: BTN8.LED1-, R26.1
unnamed: BTN8.LED2-, R27.1
unnamed: R44.2, R46.2, ROT2.B (CH_B)
unnamed: R43.2, R45.2, ROT2.A (CH_A)
unnamed: BTN4.LED1-, R22.1
unnamed: BTN4.LED2-, R23.1
unnamed: BTN5.LED1-, R28.1
unnamed: BTN5.LED2-, R29.1
unnamed: BTN2.LED1-, R15.1
unnamed: BTN1.LED1-, R8.1
unnamed: R8.2, T1.C
unnamed: R11.2, T1.B
unnamed: R15.2, T2.C
unnamed: R16.2, T2.B
POT1: C46.2, POT1.CENTER (WIPER); also elsewhere on the board
POT2: C49.2, POT2.CENTER (WIPER); also elsewhere on the board
POT3: C45.2, POT3.CENTER (WIPER); also elsewhere on the board
POT4: C48.2, POT4.CENTER (WIPER); also elsewhere on the board
POT5: C44.2, POT5.CENTER (WIPER); also elsewhere on the board
POT6: C47.2, POT6.CENTER (WIPER); also elsewhere on the board
POT7: C43.2, POT7.CENTER (WIPER); also elsewhere on the board
ROT1_A: C27.1, R39.1; also elsewhere on the board
ROT1_B: C28.1, R40.1; also elsewhere on the board
ROT1_SW: ROT1.S2 (SW2); also elsewhere on the board
ROT2_A: C29.1, R43.1; also elsewhere on the board
ROT2_B: C30.1, R44.1; also elsewhere on the board
ROT2_SW: ROT2.S2 (SW2); also elsewhere on the board

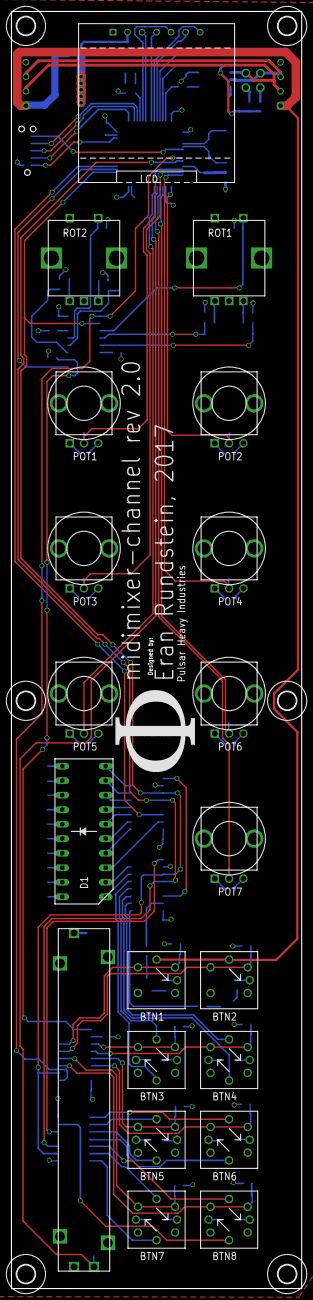
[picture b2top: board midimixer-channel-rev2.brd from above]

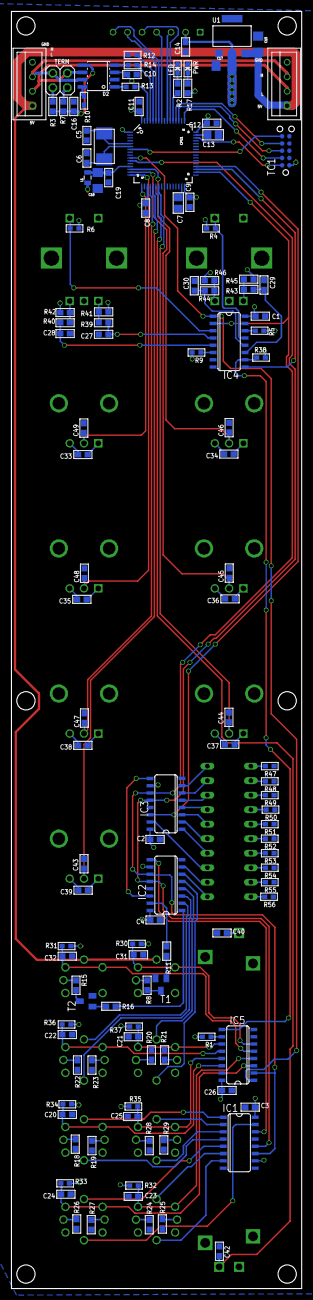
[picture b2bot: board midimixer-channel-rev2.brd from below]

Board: 2 copper layers, 50.8 x 223.5 mm, 148 parts (122 on the bottom side), 121 nets.

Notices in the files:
parts and their libraries:
microbuilder: This work is placed in the public domain, and may be freely used for commercial and non-commercial work with the following conditions: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
SparkFun-Capacitors: Licensing: Creative Commons ShareAlike 4.0 International - https://creativecommons.org/licenses/by-sa/4.0
